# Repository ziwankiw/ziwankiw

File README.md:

Zen Iwankiw
March 27, 2017

This is another line.

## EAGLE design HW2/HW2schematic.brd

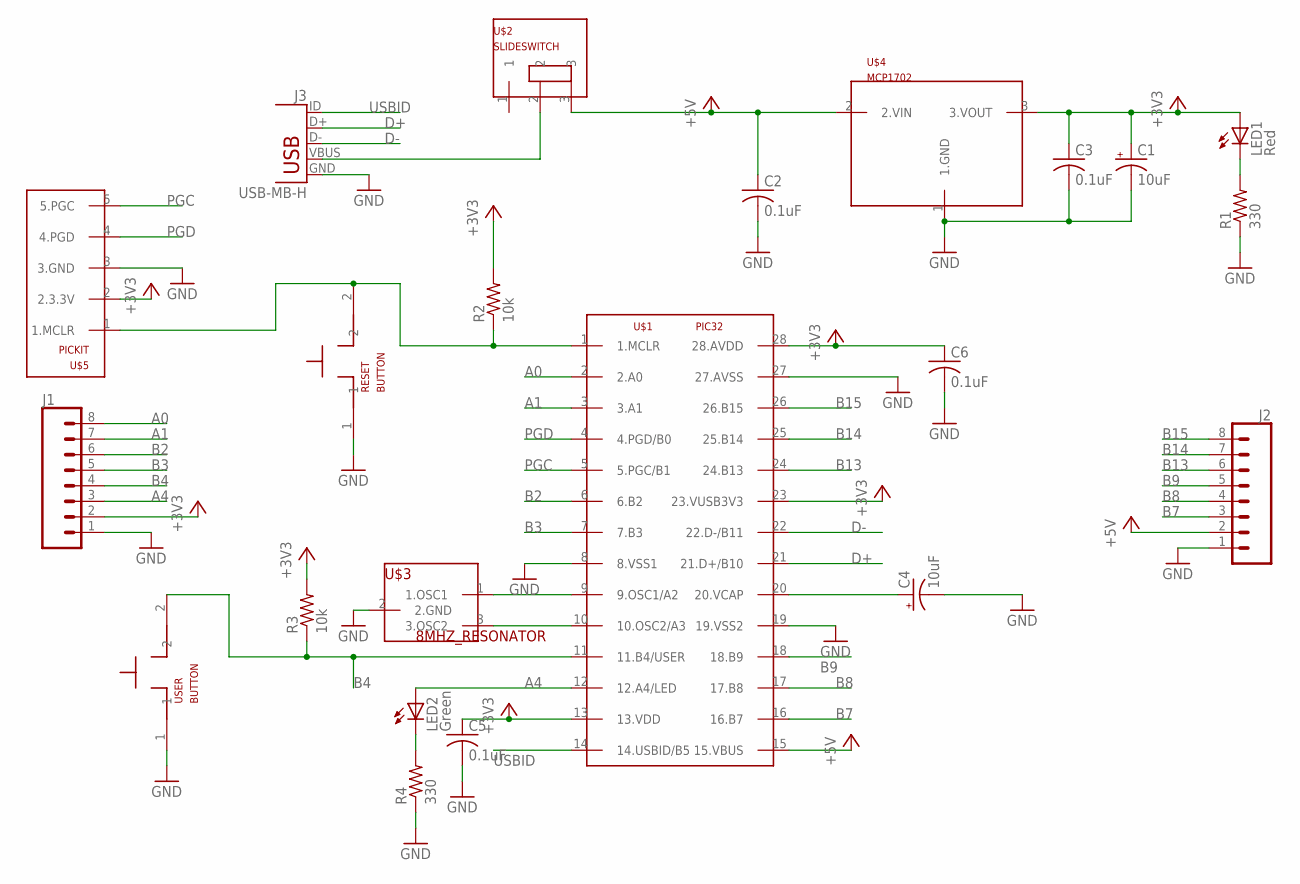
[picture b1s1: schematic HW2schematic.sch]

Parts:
C1, C4: 10uF; B45181B
C2, C3, C5, C6: 0.1uF; C025-025X050
J1, J2: CONN_08; 1X08_NO_SILK
J3: USB-MB-H
LED1: Red; LED3MM
LED2: Green; LED3MM
R1, R4: 330; 0207/10
R2, R3: 10k; 0207/10
RESET: BUTTON
U$1: PIC32; DIL28-3
U$2: SLIDESWITCH
U$3: 8MHZ_RESONATOR; 1X03
U$4: MCP1702; TO92
U$5: PICKIT
USER: BUTTON

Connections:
+3V3: C1.+, C3.1, C5.1, C6.1, J1.2, LED1.A, R2.2, R3.2, U$1.13 (13.VDD), U$1.23 (23.VUSB3V3), U$1.28 (28.AVDD), U$4.3 (3.VOUT), U$5.2 (2.3.3V)
+5V: C2.1, J2.2, U$1.15 (15.VBUS), U$2.3, U$4.2 (2.VIN)
A0: J1.8, U$1.2 (2.A0)
A1: J1.7, U$1.3 (3.A1)
A4: J1.3, LED2.A, U$1.12 (12.A4/LED)
B2: J1.6, U$1.6 (6.B2)
B3: J1.5, U$1.7 (7.B3)
B4: J1.4, R3.1, U$1.11 (11.B4/USER), USER.2
B7: J2.3, U$1.16 (16.B7)
B8: J2.4, U$1.17 (17.B8)
B9: J2.5, U$1.18 (18.B9)
B13: J2.6, U$1.24 (24.B13)
B14: J2.7, U$1.25 (25.B14)
B15: J2.8, U$1.26 (26.B15)
D+: J3.D+, U$1.21 (21.D+/B10)
D-: J3.D-, U$1.22 (22.D-/B11)
GND: C1.-, C2.2, C3.2, C4.-, C5.2, C6.2, J1.1, J2.1, J3.GND, R1.1, R4.1, RESET.1, U$1.8 (8.VSS1), U$1.19 (19.VSS2), U$1.27 (27.AVSS), U$3.2 (2.GND), U$4.1 (1.GND), U$5.3 (3.GND), USER.1
unnamed: LED2.K (C), R4.2
unnamed: R2.1, RESET.2, U$1.1 (1.MCLR), U$5.1 (1.MCLR)
unnamed: C4.+, U$1.20 (20.VCAP)
unnamed: J3.VBUS, U$2.2
unnamed: U$1.9 (9.OSC1/A2), U$3.1 (1.OSC1)
unnamed: LED1.K (C), R1.2
unnamed: U$1.10 (10.OSC2/A3), U$3.3 (3.OSC2)
PGC: U$1.5 (5.PGC/B1), U$5.5 (5.PGC)
PGD: U$1.4 (4.PGD/B0), U$5.4 (4.PGD)
USBID: J3.ID (D+1), U$1.14 (14.USBID/B5)

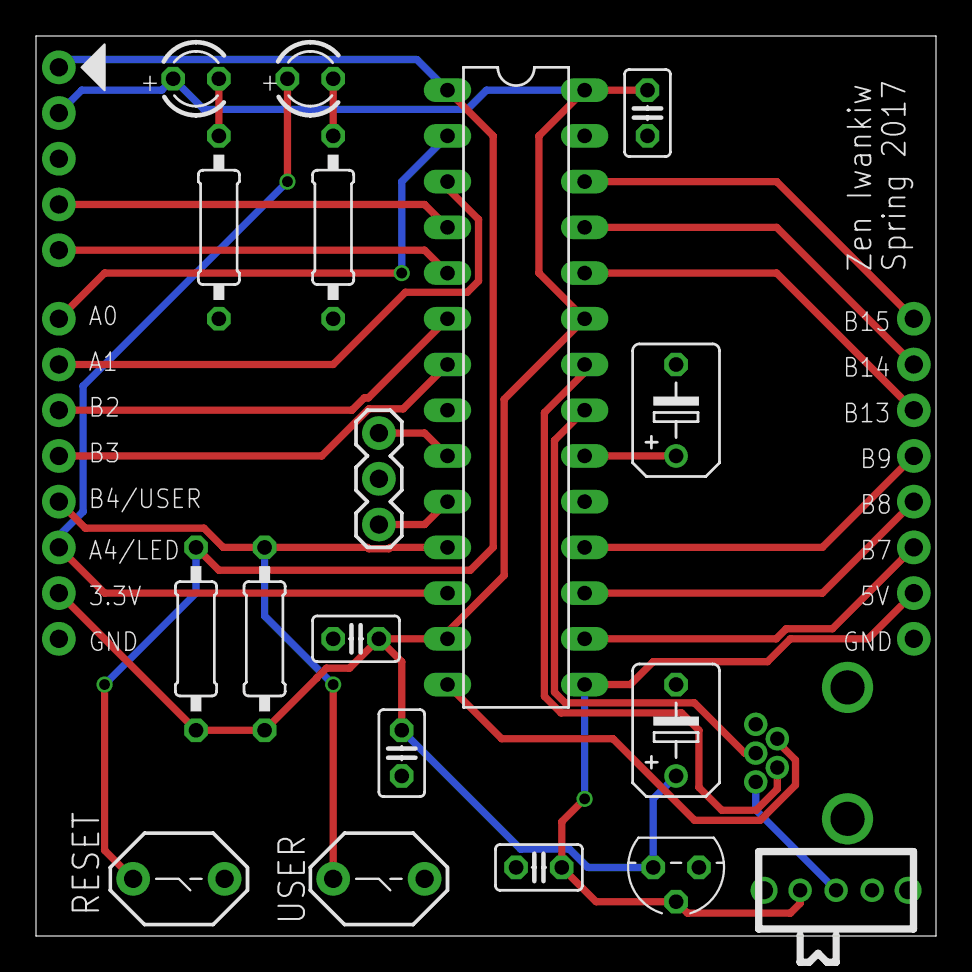
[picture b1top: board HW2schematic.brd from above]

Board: 2 copper layers, 50.0 x 50.0 mm, 22 parts (0 on the bottom side), 27 nets.

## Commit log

2017-03-27 :octocat: Added .gitattributes & .gitignore files
2017-03-27 My first commit
2017-03-27 Add another line
2017-03-27 Create files for HW1
2017-03-28 Make 3.3V regulator
    screenshots of 3.3V after adding successive capacitors
2017-03-28 adding 10uF tantalum capacitor screenshot
2017-03-29 Circuit diagrams and Photos of breadboard
2017-03-29 Write DEVCFG bits and turn on USER LED
2017-03-29 If user button is pressed, turn off LED
2017-03-29 Create 1kHz square wave on LED
    User button still turns off the LED until button is released
2017-03-29 Upload video demo
2017-04-01 Figure out how to use GitHub
2017-04-01 Change locations of USER LED and button for HW1
2017-04-01 Begin Eagle Library and Schematic
    Created voltage reg, our PIC32, and downloaded USB mini B and generic
    connectors from sparkfun. Began schematic.
2017-04-02 update schematic
    create slide switch device
2017-04-02 Begin PCB layout
2017-04-03 Update switch and button devices and optimize layout
2017-04-05 Do wire layout
2017-04-06 Finalize silkscreen, create gerber files
2017-04-06 Fix USB orientation, regenerate gerber files
2017-04-06 rename folder for HW3
2017-04-07 Create HW4 SPI project folder
2017-04-07 Configure SPI1 in spi.c and spi.h
2017-04-07 debug clock speed
2017-04-10 fix timing issues
2017-04-10 try to troubleshoot communication
2017-04-10 create triangle wave
2017-04-10 add capacitor between SPI clock and ground, troubleshoot sine function waveform
2017-04-10 Take screenshots and upload circuit diagram
2017-04-11 increase baud rate
2017-04-11 create HW5 files
2017-04-11 begin initExpander() function
2017-04-11 write to gpio and pull-up registers
2017-04-12 turn LED on
2017-04-12 read push button and turn off LED accordingly
2017-04-13 upload circuit diagram and video demo
2017-04-14 create HW6 skeleton files
2017-04-14 write drawCharacter function, write my name
2017-04-14 write drawString function. Hello World!
2017-04-14 program progress bar
2017-04-17 Add FPS reading, upload video
2017-04-19 create HW7 files
2017-04-19 write accelerometer initialization code
2017-04-19 read from WHOAMI register
2017-04-19 write read_multiple function
2017-04-19 read from multiple registers and recreate shorts from 8 bit words
2017-04-19 read out x and y accelerations on LCD
2017-04-19 draw bars corresponding to x and y accelerations
2017-04-19 upload demo video
2017-04-20 get HW1 to work using Harmony
2017-04-20 reupload HW8 code using Harmony
2017-04-25 copy Nick's usb code, upload and verify it works
2017-04-25 print accelerometer data to computer at 5Hz
2017-04-25 print accel data at 100Hz
2017-04-26 Check input for 'r', print 100 accelerometer readings
2017-04-28 copy HW9 code, make sure it still works
2017-04-28 implement MAF filter
2017-04-28 implement IIR filter
2017-04-30 implement FIR filter
2017-05-02 copy and upload default cursor circular movement code
2017-05-02 Change movement variables to constant number
2017-05-02 import and initialize i2c and imu
2017-05-02 read and scale accelerometer data, send to mouse commands
2017-05-04 troubleshoot usb connection
2017-05-04 upload Hello World Android app to phone
2017-05-09 Load and copy sample code from github page
2017-05-09 Analyze every 5 rows
2017-05-09 Print threshold value to screen
2017-05-09 Add threshold slider bar
2017-05-09 Refine layout
2017-05-09 Add threshold detection vs. blue
2017-05-10 Interface PIC with matlab
2017-05-10 upload HW10 video
2017-05-12 PIC integer/putty print code
2017-05-13 Connect pic to android
2017-05-13 send and receive slider value on button push
2017-05-18 Upload screenshots of CAD designs
2017-05-22 Upload photos of 3d printed wheel and laser cut box
2017-05-26 detect gray pixels
2017-05-31 find CoM of gray pixels, print red dot at CoM position
2017-06-02 Create CAD files for Tech Cup and begin PWM code
2017-06-02 copy sample code
2017-06-02 Drive the robot straight
2017-06-02 modify CAD design
2017-06-02 modify CAD
2017-06-02 Set darkness threshold
2017-06-03 create Tech Cup Android App
2017-06-05 Add position sensing code
2017-06-07 Combine Camera + USB apps
2017-06-08 Complete line following robot
2017-06-08 Upload video demos
2017-06-08 speed up flag waving
2017-06-09 Adjust image detection params for Tech Cup Location
